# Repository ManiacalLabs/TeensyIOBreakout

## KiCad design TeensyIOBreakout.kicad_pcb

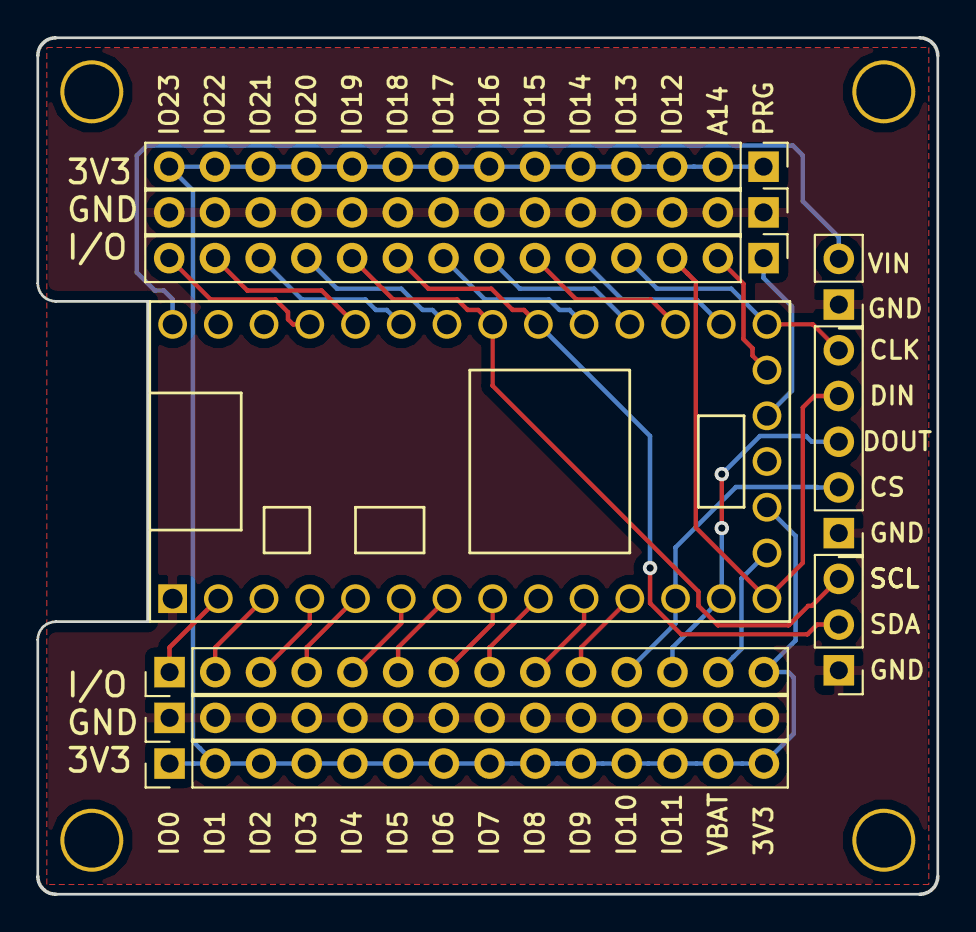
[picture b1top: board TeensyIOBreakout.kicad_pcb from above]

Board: 2 copper layers, 50.0 x 47.6 mm, 10 parts (0 on the bottom side), 30 nets.

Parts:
J1, J2, J3, J4, J8, J9: Conn_01x14_Male; Pin_Header_Straight_1x14_Pitch2.54mm
J5: Conn_01x03_Male; Pin_Header_Straight_1x03_Pitch2.54mm
J6: Conn_01x05_Male; Pin_Header_Straight_1x05_Pitch2.54mm
J7: Conn_01x02_Male; Pin_Header_Straight_1x02_Pitch2.54mm
U1: Teensy3.2; Teensy30_31_32_LC_EdgePads

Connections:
3V3: J1.14, J8.1, J8.2, J8.3, J8.4, J8.5, J8.6, J8.7, J8.8, J8.9, J8.10, J8.11, J8.12, J8.13, J8.14, J9.1, J9.2, J9.3, J9.4, J9.5, J9.6, J9.7, J9.8, J9.9, J9.10, J9.11, J9.12, J9.13, J9.14, U1.16
A14: J3.2, U1.19
GND: J2.1, J2.2, J2.3, J2.4, J2.5, J2.6, J2.7, J2.8, J2.9, J2.10, J2.11, J2.12, J2.13, J2.14, J4.1, J4.2, J4.3, J4.4, J4.5, J4.6, J4.7, J4.8, J4.9, J4.10, J4.11, J4.12, J4.13, J4.14, J5.1, J6.1, J7.1, U1.1
IO_0: J1.1, U1.2
IO_1: J1.2, U1.3
IO_2: J1.3, U1.4
IO_3: J1.4, U1.5
IO_4: J1.5, U1.6
IO_5: J1.6, U1.7
IO_6: J1.7, U1.8
IO_7: J1.8, U1.9
IO_8: J1.9, U1.10
IO_9: J1.10, U1.11
IO_10: J1.11, J6.2, U1.12
IO_11: J1.12, J6.3, U1.13
IO_12: J3.3, J6.4, U1.14
IO_13: J3.4, J6.5, U1.20
IO_14: J3.5, U1.21
IO_15: J3.6, U1.22
IO_16: J3.7, U1.23
IO_17: J3.8, U1.24
IO_18: J3.9, J5.2, U1.25
IO_19: J3.10, J5.3, U1.26
IO_20: J3.11, U1.27
IO_21: J3.12, U1.28
IO_22: J3.13, U1.29
IO_23: J3.14, U1.30
PROG: J3.1, U1.18
VBAT: J1.13, U1.15
Vin: J7.2, U1.33

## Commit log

2018-09-18 SCH and PCB layout begun
2018-09-19 Updated SCH and PCB to use fewer header footprints
2018-10-09 Added I2C, SPI headers, rear Teensy pins
2018-10-09 Made board bigger, added moutning holes, front labels
2018-10-09 Added USB cutout, fixed labels.
2018-10-10 routing :)
2018-10-10 added dimmensions to user drawing layer.
2018-10-10 Added labels to back, Sent to OSHPark for fab.
2018-11-07 Added 3V3 rail, moved I2C/SPI/VIN headers
